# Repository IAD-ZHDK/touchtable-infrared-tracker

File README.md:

# Touch Table IR Tracking System 
This project aims to create an infrared tracking system for tactile tables.

*Tracking application detecting a single tactile object.*

### Installation

#### MacOS

Just copy and past this snippet in the terminal to quickly install and start the system (only MacOS).

```bash
echo IR Tracking Quickstart

if [[ $? != 0 ]] ; then
	echo isntalling Homebrew
	ruby -e "$(curl -fsSL https://raw.githubusercontent.com/Homebrew/install/master/install)"
else
	echo Homebrew already installed!
	brew update
fi

brew install git
brew install --cask temurin

git clone https://github.com/IAD-ZHDK/IR_tracking
cd IR_tracking

echo starting...
./gradlew run

echo done
```

After the first time installation, please change into the installation folder and only run the following in the terminal:

```bash
./gradlew run
```

#### Windows

On Windows follow these steps to install the software:

```bash
# install Eclipse Temurin 17 (JDK)
winget install -e --id EclipseAdoptium.Temurin.17.JDK

# run software
gradlew.bat run
```

### Develop

#### Install and Run
Everything is installed through the [gradle](https://gradle.org/) dependency manager. To run the application, OpenJDK 11 is needed and can be installed through your favourite package manager. On MacOS we recommend to use [brew](https://brew.sh/):

```bash
brew install --cask temurin

winget install -e --id EclipseAdoptium.Temurin.17.JDK
```

Now just run the following command and gradlew will download, build and run the project.

```bash
# windows
gradlew.bat run

# macOS / unix
./gradlew run
```

### Build for Distribution
To bundle all dependencies and build the project run the following commands. This will take a bit of time because JavaCV will be added to the jar-file.

```bash
# windows
gradlew.bat clean build jpackage --info

# macOS / unix
./gradlew clean build jpackage --info
```

The built distributable can be found under `build/dist` and includes the JVM as well as all dependencies.

### How to use

#### Example
To connect with the IR tracking system it is possible to listen to predefined OSC messages. There is already a `TrackingClient` written for Processing to connect with the tracking application. Check out the [ExampleReceiver](https://github.com/IAD-ZHDK/IR_tracking/tree/master/examples/ExampleReceiver) sketch.

#### OSC Protocol
The OSC protocol sends out events which are need for the visualisation. It already normalizes and filters the values.

```java
// Add is sent if a new object is detected.

"/tracker/add"
	- uniqueId (int) // unique number
	- identifier (int) // object type
	- x-coordinate (float) // normalized
	- y-coordinate (float) // normalized
	- rotation (float) // between 0.0-180.0
	- intensity (float) // normalized
```

```java
// Every n millisecond an update is sent for each active object.

"/tracker/update"
	- uniqueId (int) // unique number
	- identifier (int) // object type
	- x-coordinate (float) // normalized
	- y-coordinate (float) // normalized
	- rotation (float) // between 0.0-180.0
	- intensity (float) // normalized
```

```java
// Remove is sent if an object is not detected anymore.

"/tracker/remove"
	- uniqueId (int) // unique number
```

### About
Developed at [Zurich University of the Arts ZHdK](https://www.zhdk.ch/) 2022

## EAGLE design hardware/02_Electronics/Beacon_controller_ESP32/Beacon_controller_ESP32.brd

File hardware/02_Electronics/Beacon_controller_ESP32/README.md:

# HARDWARE FOR IR-TRACKING TOKEN
This is a work in progross for a ESP32 based controler for IR tokens

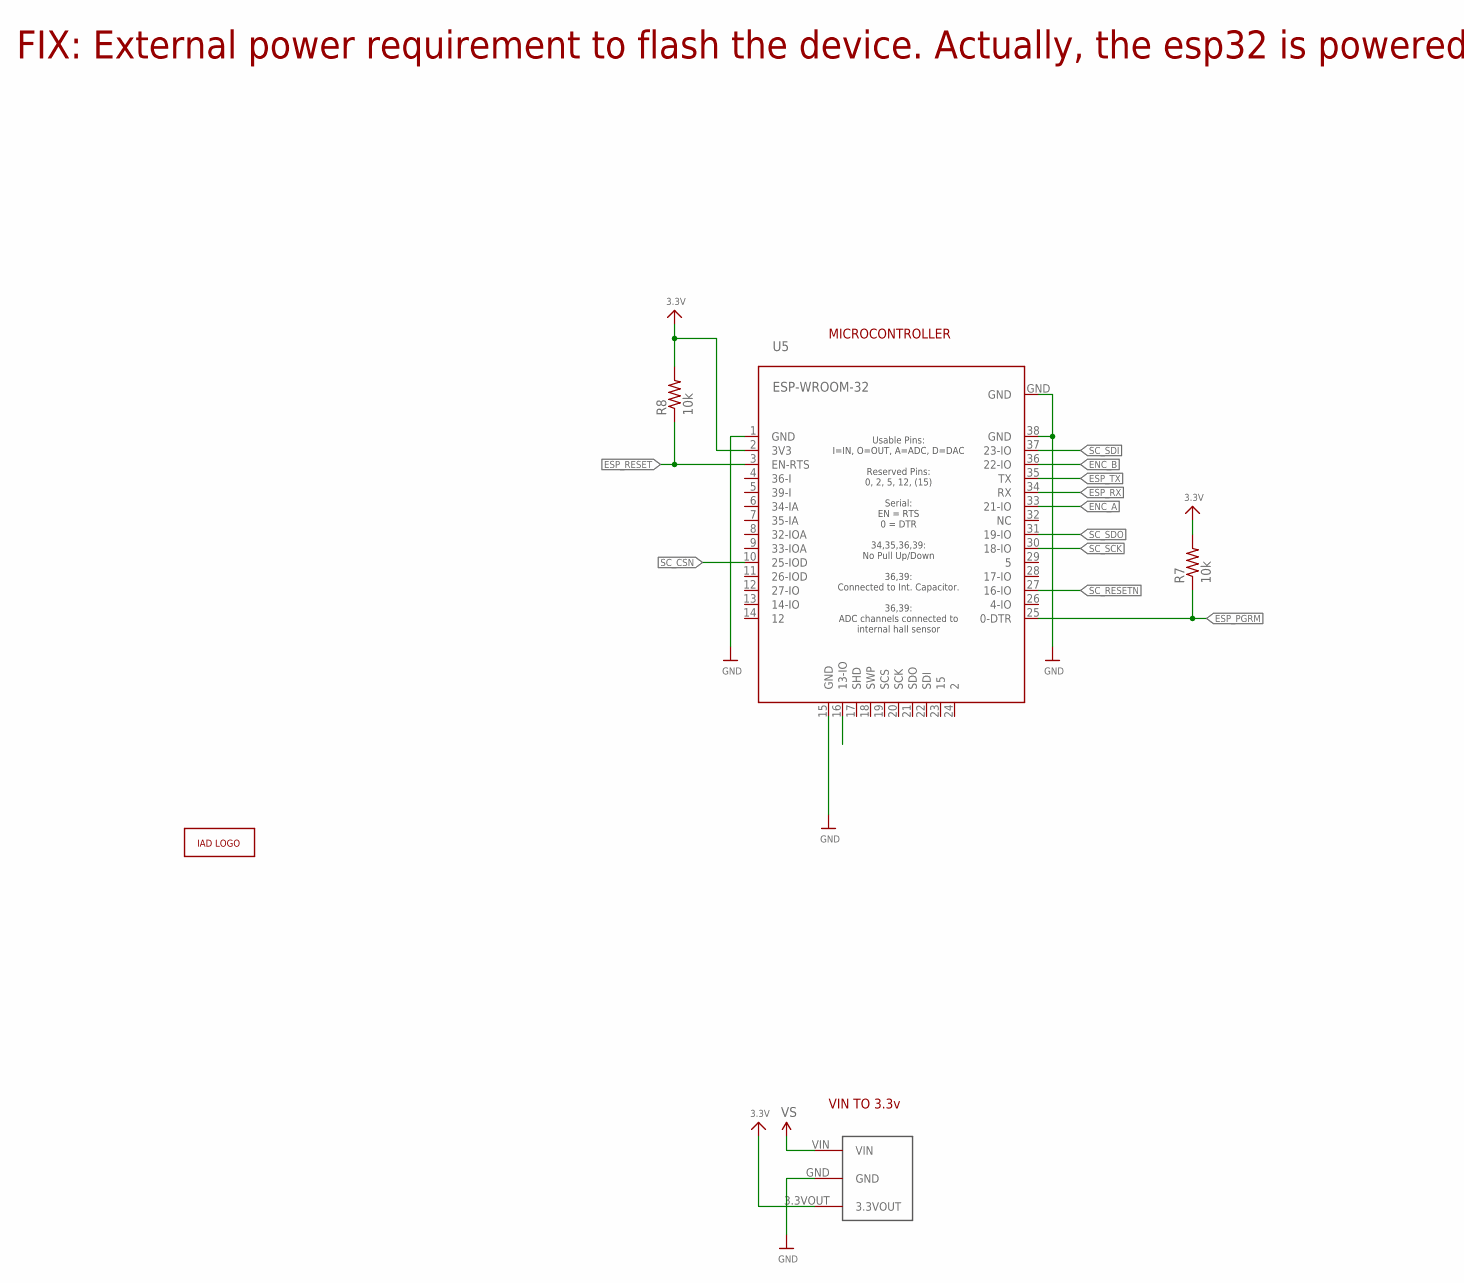
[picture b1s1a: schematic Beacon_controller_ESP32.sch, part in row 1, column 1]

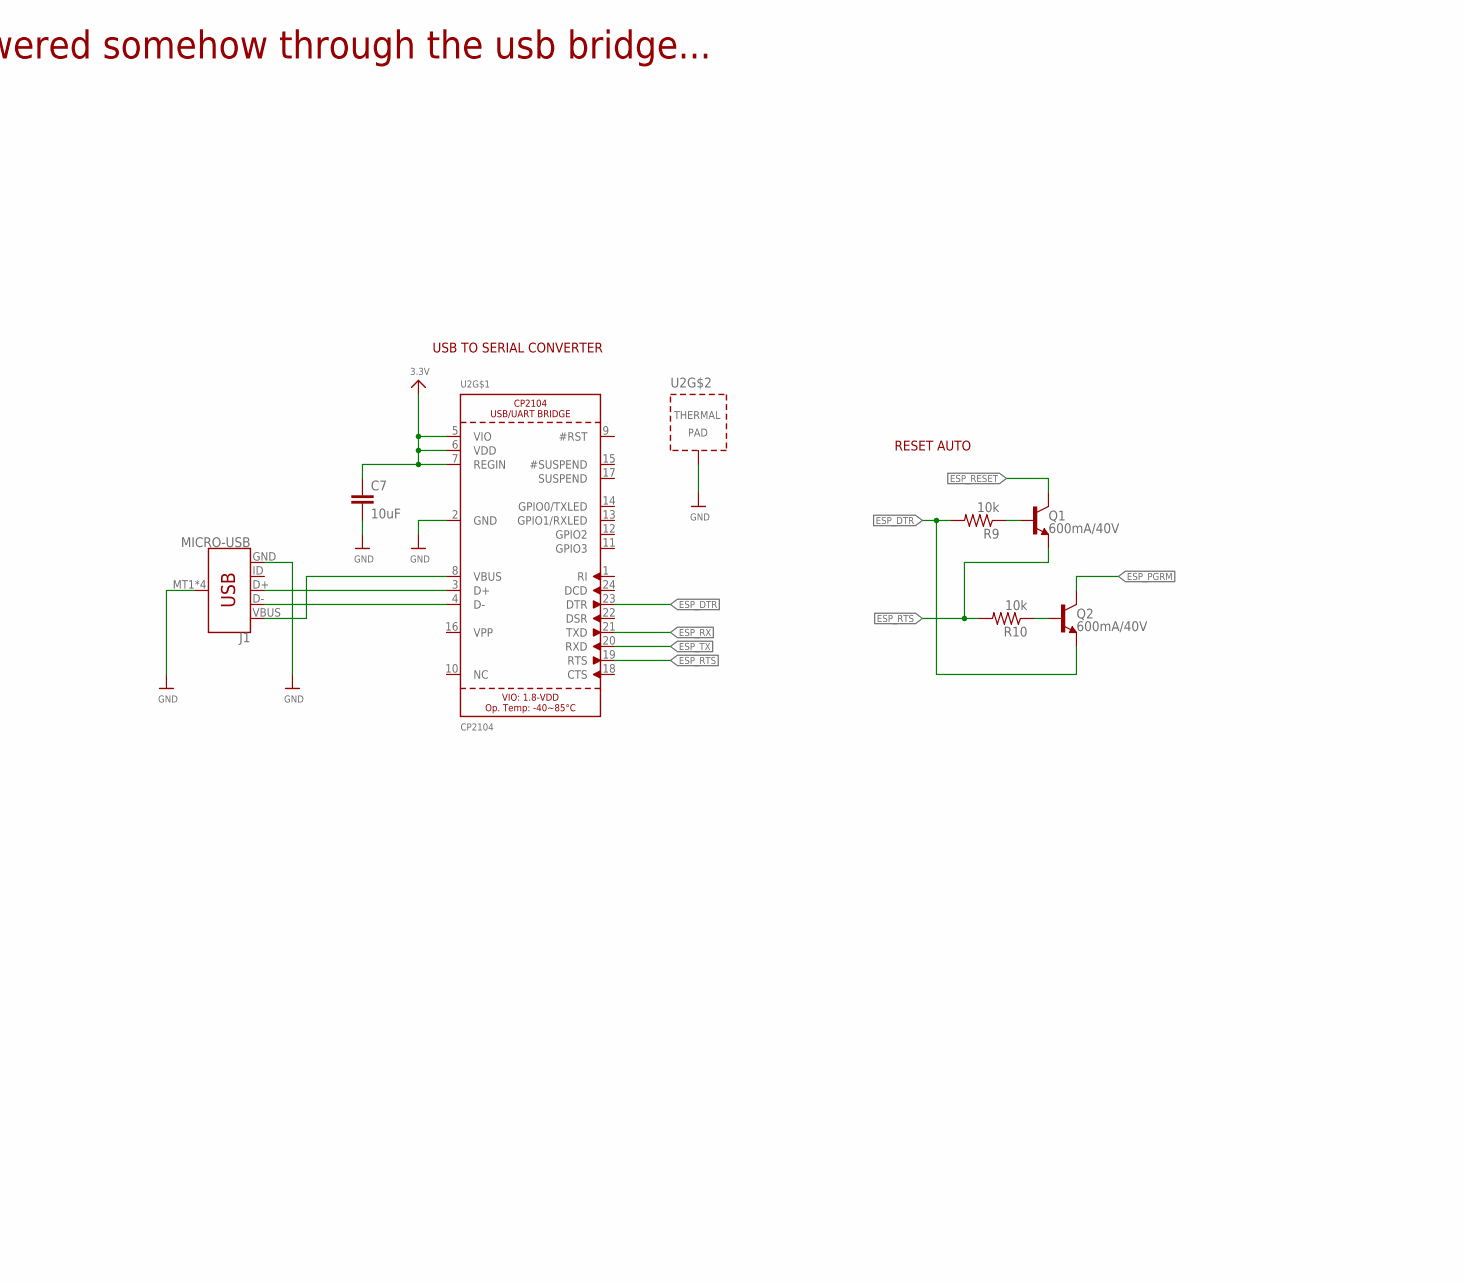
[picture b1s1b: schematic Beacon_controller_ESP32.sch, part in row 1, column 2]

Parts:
A1: ZHDK_LOGO_METAL; ZHDK_LOGO
C7: 10uF; 0603
J1: MICRO-USB; USB-MICROB
Q1, Q2: 600mA/40V; SOT23-3
R7, R8, R9, R10: 10k; 0603-RES
U2: CP2104; QFN24_4MM_SMSC
U4: TRACO12433
U5: ESP-WROOM-32

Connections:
3.3V: C7.1, R7.2, R8.2, U2.5 (VIO), U2.6 (VDD), U2.7 (REGIN), U4.3.3VOUT, U5.2 (3V3)
BTN_HOME: U5.16 (13-IO)
ENC_A: U5.33 (21-IO)
ENC_B: U5.36 (22-IO)
ESP_DTR: Q2.2 (E), R9.2, U2.23 (DTR)
ESP_PGRM: Q2.3 (C), R7.1, U5.25 (0-DTR)
ESP_RESET: Q1.3 (C), R8.1, U5.3 (EN-RTS)
ESP_RTS: Q1.2 (E), R10.2, U2.19 (RTS)
ESP_RX: U2.21 (TXD), U5.34 (RX)
ESP_TX: U2.20 (RXD), U5.35 (TX)
GND: C7.2, J1.GND, J1.MT1 (SHIELD), J1.MT2 (SHIELD), J1.P$1 (SHIELD), J1.P$2 (SHIELD), U2.2 (GND), U2.THERM (TP), U4.GND, U5.1 (GND), U5.15 (GND), U5.38 (GND), U5.GND
unnamed: J1.VBUS, U2.8 (VBUS)
unnamed: J1.D+, U2.3 (D+)
unnamed: J1.D-, U2.4 (D-)
unnamed: Q1.1 (B), R9.1
unnamed: Q2.1 (B), R10.1
SC_CSN: U5.10 (25-IOD)
SC_RESETN: U5.27 (16-IO)
SC_SCK: U5.30 (18-IO)
SC_SDI: U5.37 (23-IO)
SC_SDO: U5.31 (19-IO)
VS: U4.VIN

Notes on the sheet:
MICROCONTROLLER
RESET AUTO
VIN TO 3.3v
USB TO SERIAL CONVERTER
FIX: External power requirement to flash the device. Actually, the esp32 is powered somehow through the usb bridge...

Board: 2 copper layers, 12 parts (0 on the bottom side), 13 nets, no tracks yet.

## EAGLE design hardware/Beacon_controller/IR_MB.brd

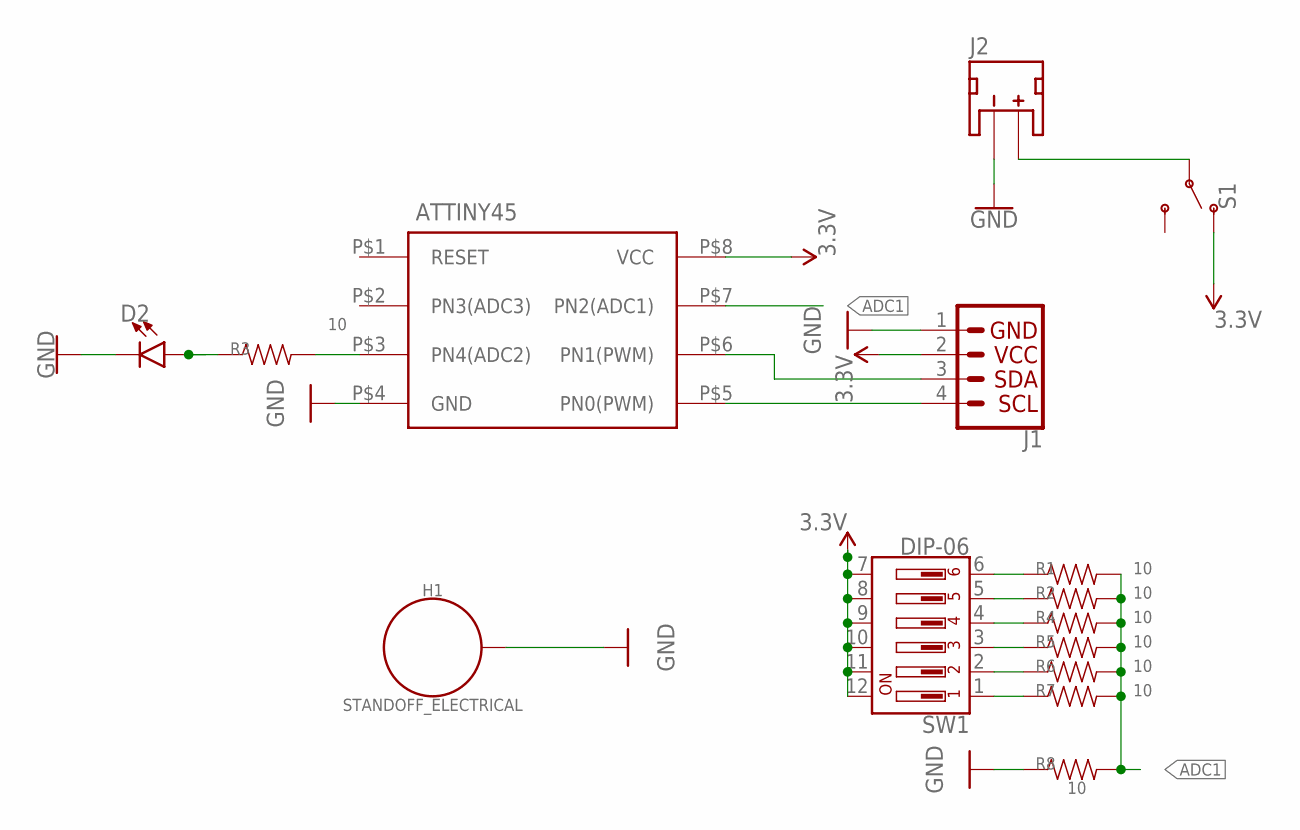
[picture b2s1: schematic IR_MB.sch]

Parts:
D2: LED-FKIT-1206; FKIT-LED-1206
H1: STANDOFF_ELECTRICAL; STANDOFF-ELECTRICAL
J1: QWIIC_CONNECTORJS-1MM; 1X04_1MM_RA
J2: JST_2MM_MALE; JST-2-SMD
R1, R2, R3, R4, R5, R6, R7, R8: 10; 1206
S1: SWITCH-SPDT-PTH-11.6X4.0MM-KIT; SWITCH_SPDT_PTH_11.6X4.0MM_KIT
SW1: DIP-06; DIPSWITCH-06-SMD
U$1: ATTINY45; 8PDIP

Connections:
3.3V: J1.2, S1.1 (O), SW1.7, SW1.8, SW1.9, SW1.10, SW1.11, SW1.12, U$1.P$8 (VCC)
ADC1: R1.2, R2.2, R4.2, R5.2, R6.2, R7.2, R8.2, U$1.P$7 (PN2(ADC1))
GND: D2.C, H1.P1, J1.1, J2.1 (-), R8.1, U$1.P$4 (GND)
unnamed: R3.2, U$1.P$3 (PN4(ADC2))
unnamed: D2.A, R3.1
unnamed: J1.4, U$1.P$5 (PN0(PWM))
unnamed: J1.3, U$1.P$6 (PN1(PWM))
unnamed: J2.2 (+), S1.2
unnamed: R1.1, SW1.6
unnamed: R2.1, SW1.5
unnamed: R4.1, SW1.4
unnamed: R5.1, SW1.3
unnamed: R6.1, SW1.2
unnamed: R7.1, SW1.1

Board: 2 copper layers, 15 parts (0 on the bottom side), 14 nets, no tracks yet.

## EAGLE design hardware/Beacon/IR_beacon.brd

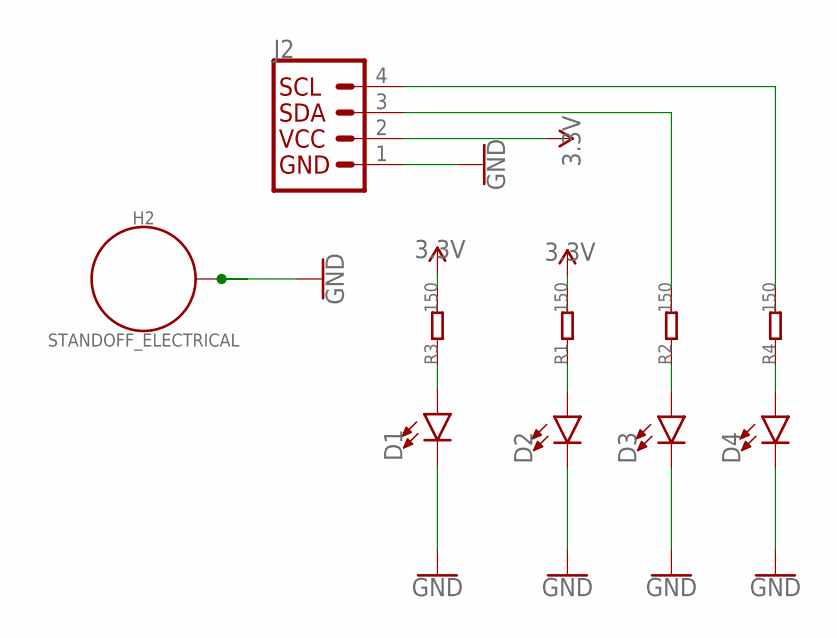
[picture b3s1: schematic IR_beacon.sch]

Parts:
D1, D2, D3, D4: LED-FKIT-1206; FKIT-LED-1206
H2: STANDOFF_ELECTRICAL; STANDOFF-ELECTRICAL
J2: QWIIC_CONNECTORJS-1MM; 1X04_1MM_RA
R1, R2, R3, R4: 150; 0603_S

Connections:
3.3V: J2.2, R1.2, R3.2
GND: D1.C, D2.C, D3.C, D4.C, H2.P1, J2.1
unnamed: J2.4, R4.2
unnamed: D1.A, R3.1
unnamed: D3.A, R2.1
unnamed: D2.A, R1.1
unnamed: D4.A, R4.1
unnamed: J2.3, R2.2

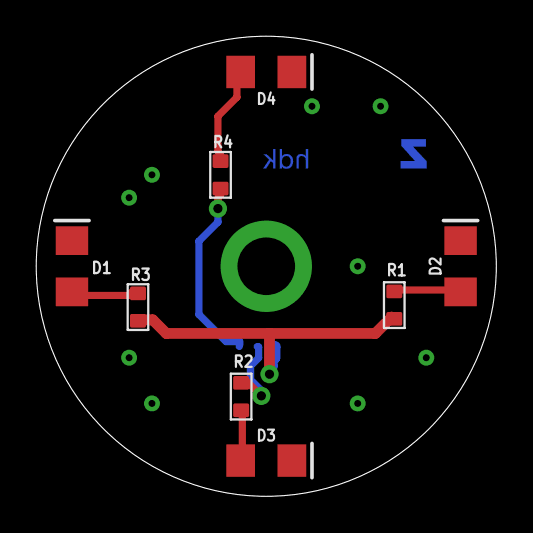
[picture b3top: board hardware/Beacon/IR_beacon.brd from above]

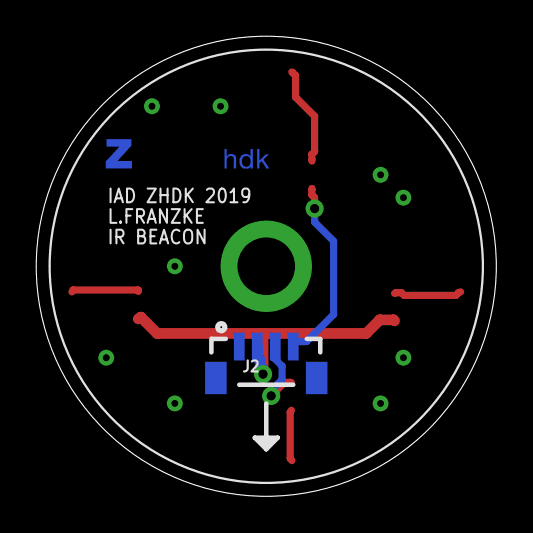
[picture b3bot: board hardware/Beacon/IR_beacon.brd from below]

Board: 2 copper layers, 25.6 x 25.6 mm, 11 parts (2 on the bottom side), 8 nets.

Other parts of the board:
U$2: ZHDK_LOGO

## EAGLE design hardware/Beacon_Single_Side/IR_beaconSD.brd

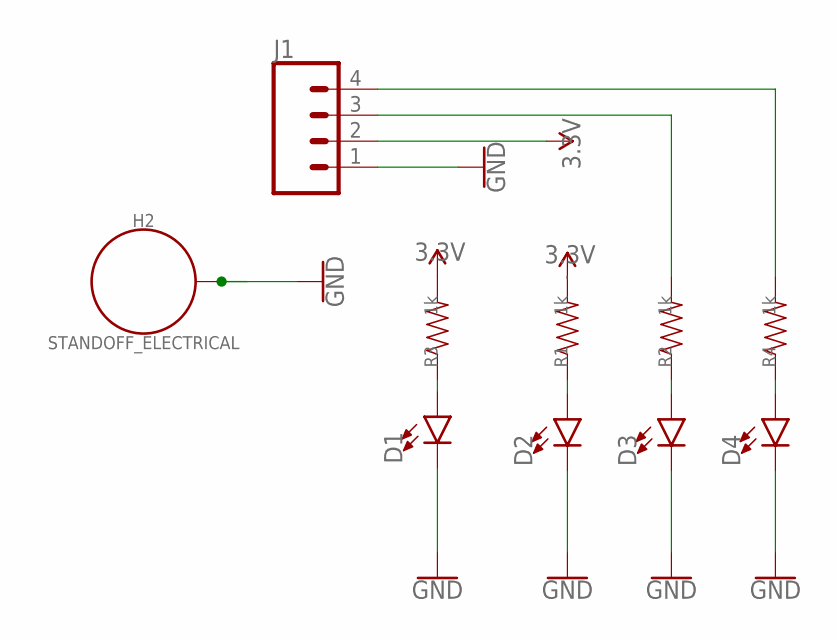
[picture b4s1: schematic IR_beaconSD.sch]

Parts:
D1, D2, D3, D4: LED-FKIT-1206; FKIT-LED-1206
H2: STANDOFF_ELECTRICAL; STANDOFF-ELECTRICAL
J1: CONN_04LONGPADS; 1X04_LONGPADS
R1, R2, R3, R4: 1k; AXIAL-0.3

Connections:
3.3V: J1.2, R1.P$2 (2), R3.P$2 (2)
GND: D1.C, D2.C, D3.C, D4.C, H2.P1, J1.1
unnamed: J1.4, R4.P$2 (2)
unnamed: D1.A, R3.P$1 (1)
unnamed: D3.A, R2.P$1 (1)
unnamed: D2.A, R1.P$1 (1)
unnamed: D4.A, R4.P$1 (1)
unnamed: J1.3, R2.P$2 (2)

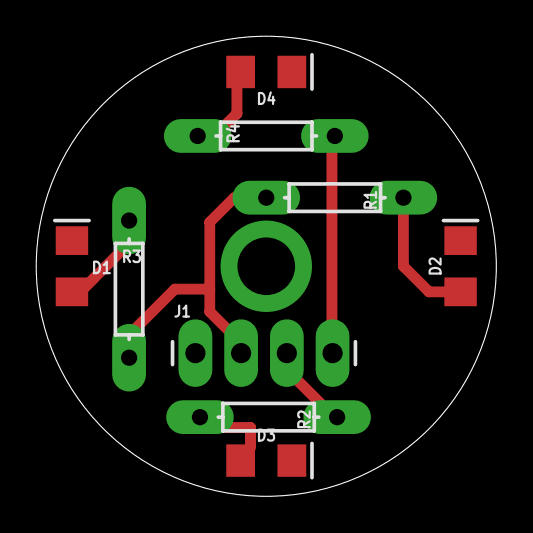
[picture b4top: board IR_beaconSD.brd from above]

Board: 2 copper layers, 25.6 x 25.6 mm, 10 parts (0 on the bottom side), 8 nets.

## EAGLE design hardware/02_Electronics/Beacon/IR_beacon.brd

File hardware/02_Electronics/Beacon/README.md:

# HARDWARE FOR IR-TRACKING TOKEN
This is a simple PCB for IR tokens, using qwiic/stemma connector for easy attachment to a micro-controller. Two LEDS are always on, with two optional for signaling and orientation.

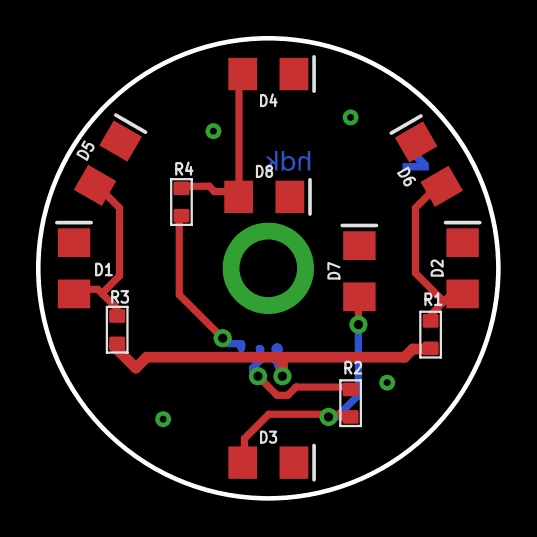
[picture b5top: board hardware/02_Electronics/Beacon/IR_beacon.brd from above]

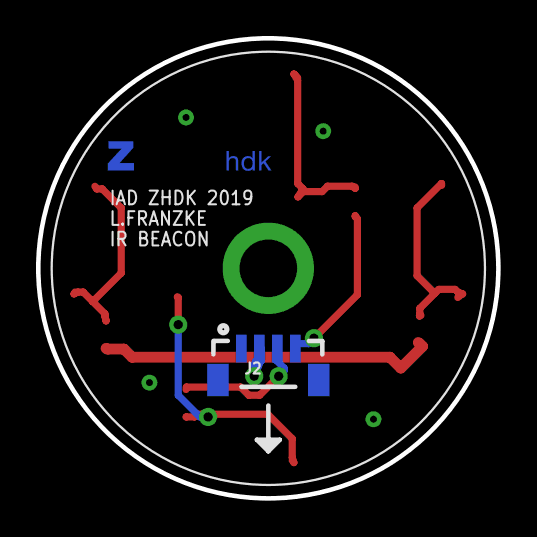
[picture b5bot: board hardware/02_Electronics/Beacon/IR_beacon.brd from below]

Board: 2 copper layers, 25.6 x 25.6 mm, 15 parts (2 on the bottom side), 8 nets.

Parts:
D1, D2, D3, D4, D5, D6, D7, D8: FKIT-LED-1206
H2: STANDOFF_ELECTRICAL; STANDOFF-ELECTRICAL
J2: 1X04_1MM_RA
R1, R2, R3, R4: 150; 0603_S
U$2: ZHDK_LOGO

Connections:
3.3V: J2.2, R1.2, R3.2
GND: D1.C, D2.C, D3.C, D4.C, D5.C, D6.C, D7.C, D8.C, H2.P1, J2.1
unnamed: J2.4, R4.2
unnamed: D1.A, D5.A, R3.1
unnamed: D3.A, D7.A, R2.1
unnamed: D2.A, D6.A, R1.1
unnamed: D4.A, D8.A, R4.1
unnamed: J2.3, R2.2

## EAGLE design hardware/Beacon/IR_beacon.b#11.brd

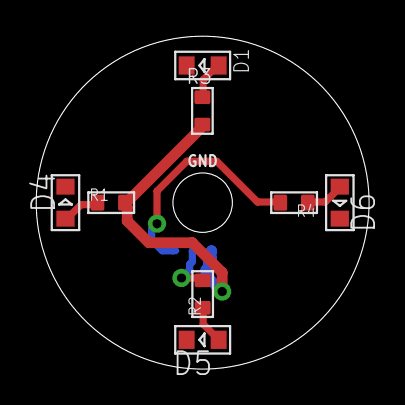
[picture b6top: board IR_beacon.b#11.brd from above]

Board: 2 copper layers, 18.5 x 18.5 mm, 11 parts (1 on the bottom side), 7 nets.

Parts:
D1: red; LED0603
D4, D5, D6: IR LED; LED0603
GND: STAND-OFF
J1: 1X04_1MM_RA
R1, R2, R3, R4: 150; 0603_S
U$2: ZHDK_LOGO

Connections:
3.3V: J1.2, R1.2, R3.2
unnamed: J1.4, R4.2
unnamed: D1.1, R3.1
unnamed: D5.1, R2.1
unnamed: D4.1, R1.1
unnamed: D6.1, R4.1
unnamed: J1.3, R2.2

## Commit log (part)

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2019-10-02 added Library files
2019-10-02 New blob detection algorythm
2019-10-02 updated blob detection (single blob)
2019-10-03 running frequency check based on variation from average.
2019-10-04 New threshold values added
2019-10-04 Threshold change
2019-10-04 added basic processing code
2019-10-04 removed some unused code
2019-10-04 changed display location
2019-10-04 implemented basic ir tracking pipeline
2019-10-04 implemented passthrough pipeline
2019-10-04 implemented working camera input
2019-10-04 created selectable input config
2019-10-05 implemented video input for testing
2019-10-05 created javacv preview to replace processing
2019-10-05 implemented simple video display
2019-10-05 implemented simple thresholding
2019-10-05 implemented morphology filter
2019-10-05 implemented component analysis
2019-10-05 added pipeline selection in ui
2019-10-05 added project publishing artefacts
2019-10-05 added distribution info
2019-10-05 implemented nearest matching
2019-10-05 implemented basic ring buffer
2019-10-05 implemented intensity tracking over frames
2019-10-05 implemented iterator for ring buffer
2019-10-05 added annotate overlay example
2019-10-05 removed annotation overlay and created settings
2019-10-05 added tracking example image
2019-10-05 implemented information about frametime
2019-10-05 added timestamp to active region
2019-10-05 added contour methods
2019-10-05 implemented basic shape tracking
2019-10-05 added area display
2019-10-06 refactored pipeline concept and added subpipelines
2019-10-06 limited osc output to fps frequency
2019-10-06 added osc receiver example
2019-10-06 added normalization
2019-10-06 removed normalization
2019-10-06 updated example to use normalized positions
2019-10-06 fixed timer issue and added better framerate block
2019-10-06 implemented adaptive threshold margin
2019-10-06 implemented full sampling
2019-10-06 refactored binary detection
2019-10-07 implemented binary id detection
2019-10-07 added identifier to visualisation
2019-10-07 fixed binary conversion
2019-10-07 added comments to gap detection and fixed sample time
2019-10-07 tried to fix detection
2019-10-07 added filip correction to low and stop detection
2019-10-07 added natural threshold detection
2019-10-07 implemented life detection of pattern
2019-10-07 removed margin gap
2019-10-07 added movie creator for binary ids and proved pipeline
2019-10-08 fixed concurrency bug by removing visual input
2019-10-09 changed osc output
2019-10-09 updated to openjdk 11 and openjfx
2019-10-09 fixed app denpendencies
2019-10-09 changed install to java11
2019-10-09 implemented restart possibility
2019-10-09 added osc output
2019-10-09 made CV preview a singleton object
2019-10-09 enabled osc broadcast fixes #3
2019-10-09 added new osc initialisation and timing fixes #6
2019-10-09 tried to fix input frame concurrency issue
2019-10-09 implemented basic realsense support
2019-10-09 added passthrough pipeline if an error occures
2019-10-10 tried to implement realsense support but rs2 is not supported atm #12
2019-10-15 fixed id updating error
2019-10-15 added not working realsense2 wrapper
2019-10-15 added check if mat has to be converted
2019-10-15 udpated to rs2 device
2019-10-15 removed javafx platform runlater into ui
2019-10-15 implemented open and close for input providers
2019-10-15 added explicit waiting for pipelinethread and stop
2019-10-15 created soft shutdown
2019-10-15 removed cv view methods
2019-10-15 added ultra fast realsense
2019-10-15 implemented ir emitter setting
2019-10-15 implemented save input frame
2019-10-15 added example image for input
2019-10-15 implemented OTSU threshold
2019-10-15 added with and height to input provider after load
2019-10-15 implemented slow bitmap output
2019-10-15 fixed output writing
2019-10-15 removed visual config
2019-10-15 implemented error and message log
2019-10-15 created own parameter for reach input device
2019-10-15 renamed in config
2019-10-15 fixed pipeline startup error
2019-10-15 cloned input
2019-10-15 removed circle
2019-10-15 fixed concurrency bug with in sync cloning
2019-10-15 fixed updating frame size for normalisation
2019-10-15 changed pipeline lock to be stored in cv preview
2019-10-15 removed polydp settings
2019-10-17 added kotlin math to project
2019-10-17 added float property fields
2019-10-17 implemented simple edge selection
2019-10-17 implemented button disable while action
2019-10-17 implemented screen selection #13
2019-10-17 implemented simple mapping drawing
2019-10-17 implemented basic screen mapping with rectangle
2019-10-17 added comments for new object
2019-10-17 added ugly fix
2019-10-17 implemented simple life time check
2019-10-17 added more debugging statements
2019-10-17 removed unecessary update and added reset uinque id
2019-10-17 fixed canvas position shift
2019-10-17 releasing input mat to free storage
2019-10-17 using countdownledge for startup detection
2019-10-17 implemented gamma correction for pre-processing
2019-10-17 fixed gamma correction range
2019-10-17 redesigned label
2019-10-17 implemented dual channel ir
2019-10-18 enabled rgb input for ir camera
2019-10-18 implemented save restart of pipeline
2019-10-18 fixed gamma correction lookup table recreation concurrency bug
2019-10-18 added librealsense dependencies for all os
2019-10-18 implemented timekeeper for millis
2019-10-18 removed comment about resetting lookup table
2019-10-18 fixed object dead tracking notification
2019-10-18 copied input mat to avoid jvm crash when no object was detected in the beginning
2019-10-18 implemented new screen drawing with buffer
2019-10-18 fixed import error
2019-10-18 implemented drawing text to the screen
2019-10-18 check if pipeline is up after first frame has been rendered
2019-10-18 added more readable error messages to composition
2019-10-19 resetting unique id on pipeline restart
2019-10-19 added todos
2019-10-19 used semaphore for frame draw waiting
2019-10-20 removed pipeline drawing completly if not shown
2019-10-20 implemented basic javafx preview
2019-10-20 replaced countdown ledges with semaphores
2019-10-20 switched pipeline to use time based measurements for object state
2019-10-20 restrict osc message updating only to active objects
2019-10-20 updated readme and added OSC protocol definition
2019-10-20 added very basic tracking example
2019-10-22 added broadcast enabled library and logger for OSC
2019-10-22 implemented color detection
2019-10-22 implemented average pixel detection
2019-10-23 added new test image
2019-10-23 added area size filter (pixel based)
2019-10-25 Code for Beacon Hardware added
2019-10-25 Ignore Eagle autosave files
2019-10-25 fixed range slider bug
2019-10-30 added basic demo (without out of screen)
2019-10-30 updated out of bounds
2019-10-30 fixed rotation
2019-10-30 Revert "fixed visu"
    This reverts commit e460d9fe7930bc57a3456d524d0ee81b27c04307.
2019-10-30 added cursor hide and show
2019-11-12 removed ir sensor method
2019-11-12 added basic landscape demo
2019-11-12 removed rotation
2019-11-12 renamed tactile object to marker
2019-11-12 added marker tracking
2019-11-12 split tactile device and maker apart
2019-11-12 implemented basic tracking of markers
2019-11-12 implemented rotation in visualisation
2019-11-13 implemented more accurate marker to region solver
2019-11-13 implemented stable marker detection
2019-11-14 added new point matcher
2019-11-14 added clusterer
2019-11-16 implemented tactile device tracking
2019-11-16 fixed calibration
2019-11-16 added position output as number
2019-11-16 tactile objects are adding up
2019-11-16 implemented basic tracking system
2019-11-17 implemented basic angle calculation
2019-11-19 lowered detection clustering
2019-11-19 added simple orientation detection
2019-11-20 Finished Cad files for beacon, and added new 5 bit patern for markers.
2019-11-22 enabled rotation of text
2019-11-27 Added Multitouch Demo
2019-12-04 Added new exeriments to examples
2019-12-04 tidy up of cesium
2019-12-04 cesium fix
2019-12-04 added communication
2019-12-04 implemented basic sphere
2019-12-04 implemented bump map
2019-12-04 added highres textures
2019-12-04 added post fx bloom
2019-12-05 used high res bump map
2019-12-05 Minor fixes
2019-12-06 updated multiouch demo p5js
2019-12-06 new angle tolorance
2019-12-06 added night eart
2020-03-07 switched to bildspur base and ui libraries
2020-03-07 updated version number for install
2020-03-07 added error message description to web route
2020-03-08 implemeneted osc over websocket
2020-03-11 enable auto-exposure
2020-06-30 added missing branches
2020-07-07 added adopt jdk and fixed librealsense dependencies
2020-07-07 added ffmpeg support for camera and video input
2020-07-07 fixed websocket output
2020-07-07 enabled sensor options
2020-07-07 added demo image
2020-07-07 implemented binarization methods
2020-07-07 implemented adaptiveness parameter
2020-07-08 added marker tracking video
2020-07-22 added esp32 based tactile device
2020-07-22 added basic logging library
2020-07-22 added basic logging lib
2020-07-22 Old updates to experiments pushed to remote
2020-07-23 removed verbose logging of ffmpeg
2020-07-23 setup of ESP powered beacon
2020-07-31 updates to esp32 beacon
2020-08-11 switched scan response to true
2020-08-12 implemented library byte order data reading for neopixel values
2020-08-13 added perspective transform calibration
2020-08-13 cleaned expose
2020-08-13 added websocket config
2020-08-14 using pre-solved transformation matrix for calibration
2020-08-18 Updated Hardware
2020-08-20 implemented very basic ble scanning
2020-08-20 implemented logic for ir setting into bletactile device
2020-08-21 added ble support for device identification
2020-08-21 implemented ble matching with tactile device
2020-08-21 cleaned up pipeline
2020-08-21 Updated device ID UUID
2020-08-21 implemented reading identifier
2020-08-21 upgraded gradle to version 6.0
2020-08-21 fixed timing issue of mapping
2020-08-21 fixed fast iterating of mapping
2020-08-21 added new debug info
2020-08-21 fixed visualisation
2020-08-21 added unmapping to mapping method
2020-08-21 added unmatch behaviour if device is not connected anymore over ble
2020-09-17 implemented verbose logging for BLE service
2020-09-17 implemented primitive rendering
2020-09-17 switched to hbox instead of border pane
2020-09-17 implemented basic annotation
2020-09-17 incresead size and set font rendering
2020-09-17 fixed text rendering
2020-09-18 added comment for canvas ratio
2020-09-21 implemented new calibration wizard
2020-09-21 added cancel button for calibration wizard
2020-09-21 added travis configuration
2020-09-21 fixed invalid chars in javadoc
2020-09-22 excluded windows ci build
    because it's not support by travis
2020-10-22 implemented very basic window resizing based on preview
2020-10-22 fixed interactive tracker if window is resized
2020-10-22 renamed parameter in config
2020-10-22 fixed auto resize on load
2020-11-10 added quick start example
2020-11-29 updated bildspur base libraries
2021-02-16 clean up of pipeline imports
2021-04-26 implemented smoothing option for tracking
2021-04-26 implemented angle smoothing
2021-06-29 implemented a color tracking pipeline
2022-10-04 Cleaned up examples
2022-10-04 removed serial outputs
2022-10-20 updated to gradle 7 and jdk 17
2022-10-20 fixed osx installation file
2022-10-20 updated javacpp libraries to 1.5.7 to support most recent realsense models
2022-10-27 closing application if port is already in use
2022-10-27 changed websocket port
2022-10-27 fixed arm64 apple silicon support
2022-10-27 added build support for app images
2022-10-27 reformatted gradle file
2022-11-01 implemented resizable window support
2022-11-01 updated readme for jpackage build
2022-11-11 implemented support for external file loading(video and image)

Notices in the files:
parts and their libraries:
SparkFun-LED: Licensing: Creative Commons ShareAlike 4.0 International - https://creativecommons.org/licenses/by-sa/4.0
SparkFun-Capacitors: Licensing: CC v3.0 Share-Alike You are welcome to use this library for commercial purposes.
